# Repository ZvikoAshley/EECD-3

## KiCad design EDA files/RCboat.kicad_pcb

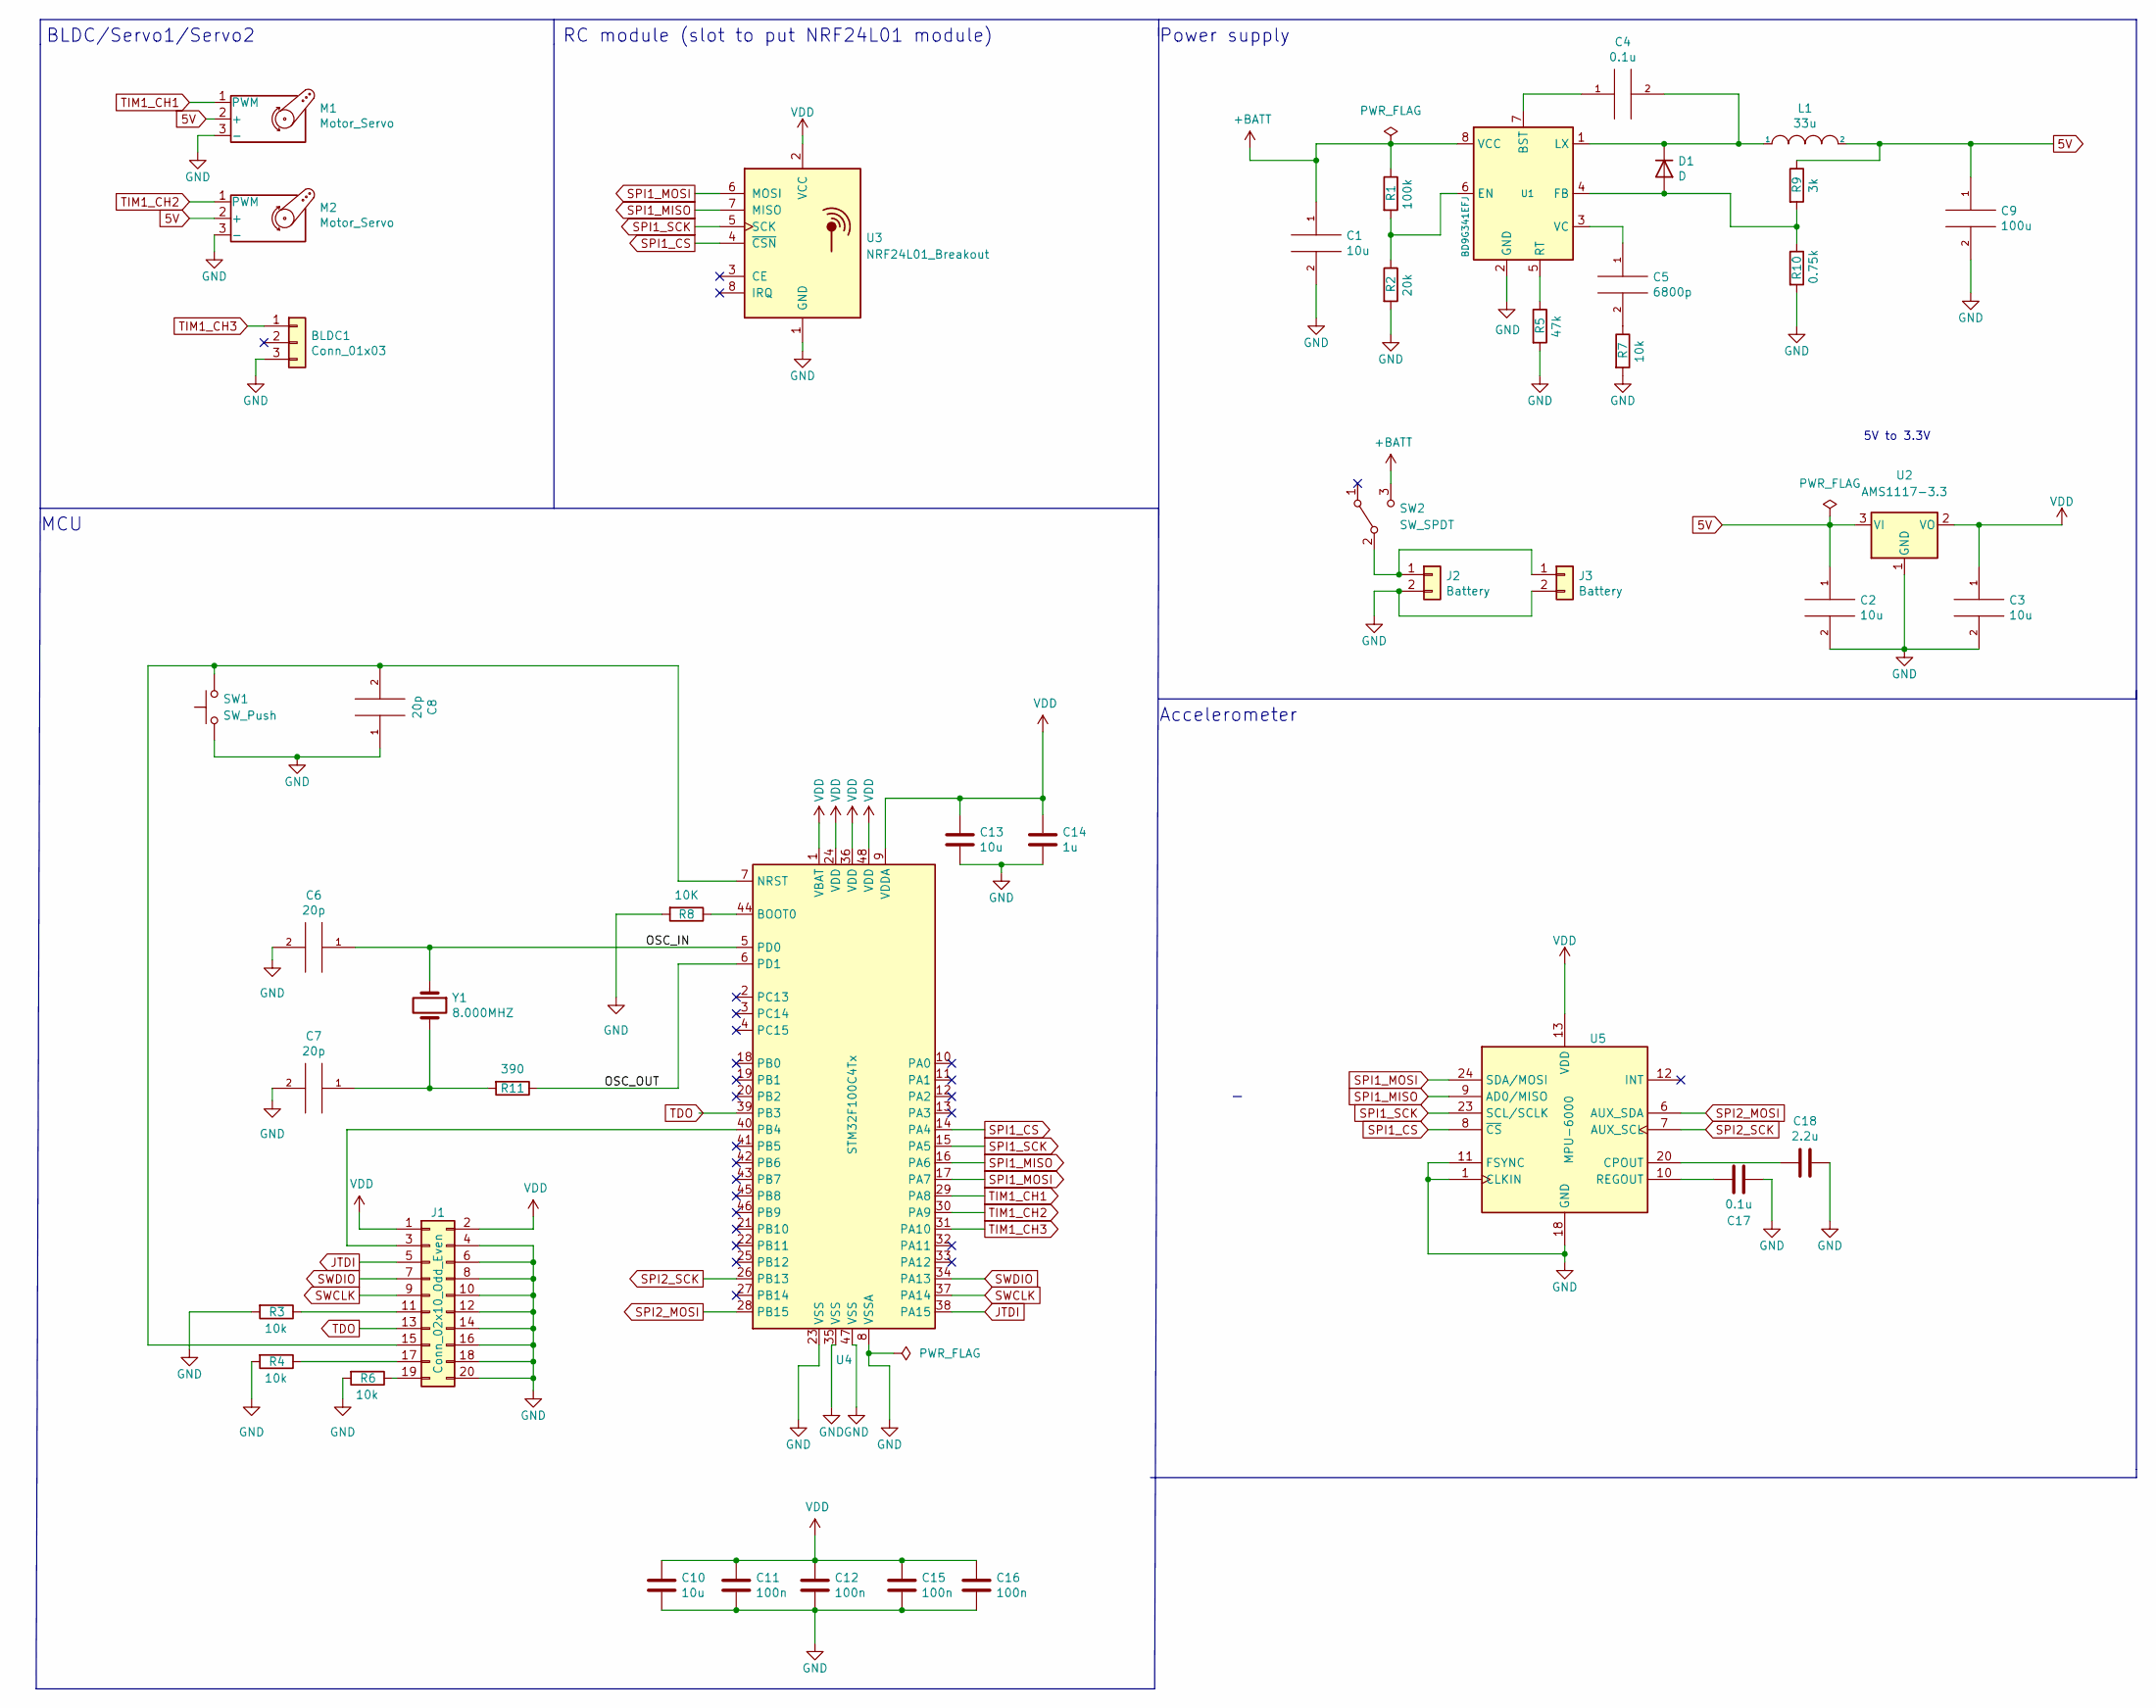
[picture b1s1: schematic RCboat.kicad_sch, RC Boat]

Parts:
BLDC1: Conn_01x03; PinHeader_1x03_P2.54mm_Vertical
C1, C2, C3, C10, C13: 10u; D_0603_1608Metric_Pad1.05x0.95mm_HandSolder
C4, C17: 0.1u; D_0603_1608Metric_Pad1.05x0.95mm_HandSolder
C5: 6800p; D_0603_1608Metric_Pad1.05x0.95mm_HandSolder
C6, C7, C8: 20p; D_0603_1608Metric_Pad1.05x0.95mm_HandSolder
C9: 100u; D_0603_1608Metric_Pad1.05x0.95mm_HandSolder
C11, C12, C15, C16: 100n; D_0603_1608Metric_Pad1.05x0.95mm_HandSolder
C14: 1u; D_0603_1608Metric_Pad1.05x0.95mm_HandSolder
C18: 2.2u; D_0603_1608Metric_Pad1.05x0.95mm_HandSolder
D1: D; D_1206_3216Metric_Pad1.42x1.75mm_HandSolder
J1: Conn_02x10_Odd_Even; PinHeader_2x10_P2.54mm_Vertical
J2, J3: Battery; AMASS_XT30U-F_1x02_P5.0mm_Vertical
L1: 33u; L_0603_1608Metric_Pad1.05x0.95mm_HandSolder
M1, M2: Motor_Servo; PinHeader_1x03_P2.54mm_Vertical
R1: 100k; R_0603_1608Metric_Pad0.98x0.95mm_HandSolder
R2: 20k; R_0603_1608Metric_Pad0.98x0.95mm_HandSolder
R3, R4, R6, R7: 10k; R_0603_1608Metric_Pad0.98x0.95mm_HandSolder
R5: 47k; R_0603_1608Metric_Pad0.98x0.95mm_HandSolder
R8: 10K; R_0603_1608Metric_Pad0.98x0.95mm_HandSolder
R9: 3k; R_0603_1608Metric_Pad0.98x0.95mm_HandSolder
R10: 0.75k; R_0603_1608Metric_Pad0.98x0.95mm_HandSolder
R11: 390; R_0603_1608Metric_Pad0.98x0.95mm_HandSolder
SW1: SW_Push; SW_PUSH_6mm
SW2: SW_SPDT; SW_Slide_1P2T_CK_OS102011MS2Q
U1: BD9G341EFJ; HTSOP-8-1EP_3.9x4.9mm_P1.27mm_EP2.4x3.2mm_ThermalVias
U2: AMS1117-3.3; SOT-223-3_TabPin2
U3: NRF24L01_Breakout; PinHeader_2x04_P2.54mm_Vertical
U4: STM32F100C4Tx; LQFP-48_7x7mm_P0.5mm
U5: MPU-6000; InvenSense_QFN-24_4x4mm_P0.5mm
Y1: 8.000MHZ; Crystal_SMD_0603-2Pin_6.0x3.5mm_HandSoldering

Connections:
5V: C2.1, C9.1, L1.2, M1.2 (+), M2.2 (+), R9.1, U2.3 (VI)
+BATT: C1.1, R1.1, SW2.3 (C), U1.8 (VCC)
/OSC_IN: C6.1, U4.5 (PD0), Y1.1
/OSC_OUT: R11.1, U4.6 (PD1)
GND: BLDC1.3, C1.2, C2.2, C3.2, C6.2, C7.2, C8.1, C9.2, C10.2, C11.2, C12.2, C13.2, C14.2, C15.2, C16.2, C17.2, C18.2, J1.4, J1.6, J1.8, J1.10, J1.12, J1.14, J1.16, J1.18, J1.20, J2.2, J3.2, M1.3 (-), M2.3 (-), R2.2, R3.2, R4.2, R5.2, R6.2, R7.2, R8.2, R10.2, SW1.1, U1.2 (GND), U2.1 (GND), U3.1 (GND), U4.8 (VSSA), U4.23 (VSS), U4.35 (VSS), U4.47 (VSS), U5.1 (CLKIN), U5.11 (FSYNC), U5.18 (GND)
JTDI: J1.5, U4.38 (PA15)
unnamed: C4.1, U1.7 (BST)
unnamed: C4.2, D1.1 (K), L1.1, U1.1 (LX)
unnamed: C5.1, U1.3 (VC)
unnamed: C5.2, R7.1
unnamed: C7.1, R11.2, Y1.2
unnamed: C8.2, J1.15, SW1.2, U4.7 (NRST)
unnamed: C17.1, U5.10 (REGOUT)
unnamed: C18.1, U5.20 (CPOUT)
unnamed: D1.2 (A), R9.2, R10.1, U1.4 (FB)
unnamed: J1.3, U4.40 (PB4)
unnamed: J1.11, R3.1
unnamed: J1.17, R4.1
unnamed: J1.19, R6.1
unnamed: J2.1, J3.1, SW2.2 (B)
unnamed: R1.2, R2.1, U1.6 (EN)
unnamed: R5.1, U1.5 (RT)
unnamed: R8.1, U4.44 (BOOT0)
SPI1_CS: U3.4 (~CSN), U4.14 (PA4), U5.8 (~CS)
SPI1_MISO: U3.7 (MISO), U4.16 (PA6), U5.9 (AD0/MISO)
SPI1_MOSI: U3.6 (MOSI), U4.17 (PA7), U5.24 (SDA/MOSI)
SPI1_SCK: U3.5 (SCK), U4.15 (PA5), U5.23 (SCL/SCLK)
SPI2_MOSI: U4.28 (PB15), U5.6 (AUX_SDA)
SPI2_SCK: U4.26 (PB13), U5.7 (AUX_SCL)
SWCLK: J1.9, U4.37 (PA14)
SWDIO: J1.7, U4.34 (PA13)
TDO: J1.13, U4.39 (PB3)
TIM1_CH1: M1.1 (PWM), U4.29 (PA8)
TIM1_CH2: M2.1 (PWM), U4.30 (PA9)
TIM1_CH3: BLDC1.1, U4.31 (PA10)
VDD: C3.1, C10.1, C11.1, C12.1, C13.1, C14.1, C15.1, C16.1, J1.1, J1.2, U2.2 (VO), U3.2 (VCC), U4.1 (VBAT), U4.9 (VDDA), U4.24 (VDD), U4.36 (VDD), U4.48 (VDD), U5.13 (VDD)

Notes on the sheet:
BLDC/Servo1/Servo2
Power supply
MCU
RC module (slot to put NRF24L01 module)
5V to 3.3V
Accelerometer

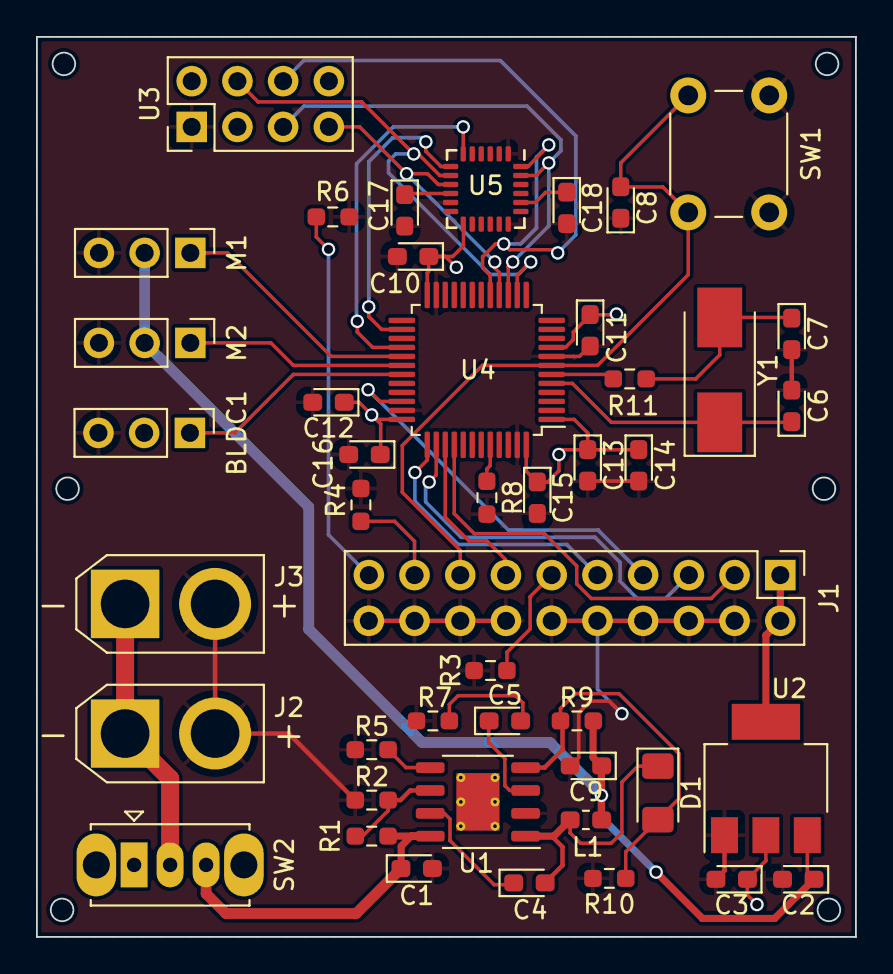
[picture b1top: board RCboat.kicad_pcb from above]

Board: 2 copper layers, 45.5 x 50.0 mm, 45 parts (0 on the bottom side), 36 nets.

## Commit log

2022-10-17 Add files via upload
    The components list
2022-10-25 Update componets
    Power supply
2022-10-28 Update componets
2022-11-07 Add files via upload
    Draft schematic in ms paint
2022-11-29 KiCad Files
    This is the KiCad schematic, When you update it please upload it ASAP
2022-12-29 Add files via upload
    updated files of schematic(mcu still in progress)
2023-01-06 Add files via upload
    The recent files of the updated schematic, (few footprints)
2023-01-14 Add files via upload
    recent files of the schemes
2023-01-21 Create Walid_pcb_design
